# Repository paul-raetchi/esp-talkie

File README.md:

# esp-talkie
ESP8266-based WiFi 802.11b/g/n Walkie Talkie

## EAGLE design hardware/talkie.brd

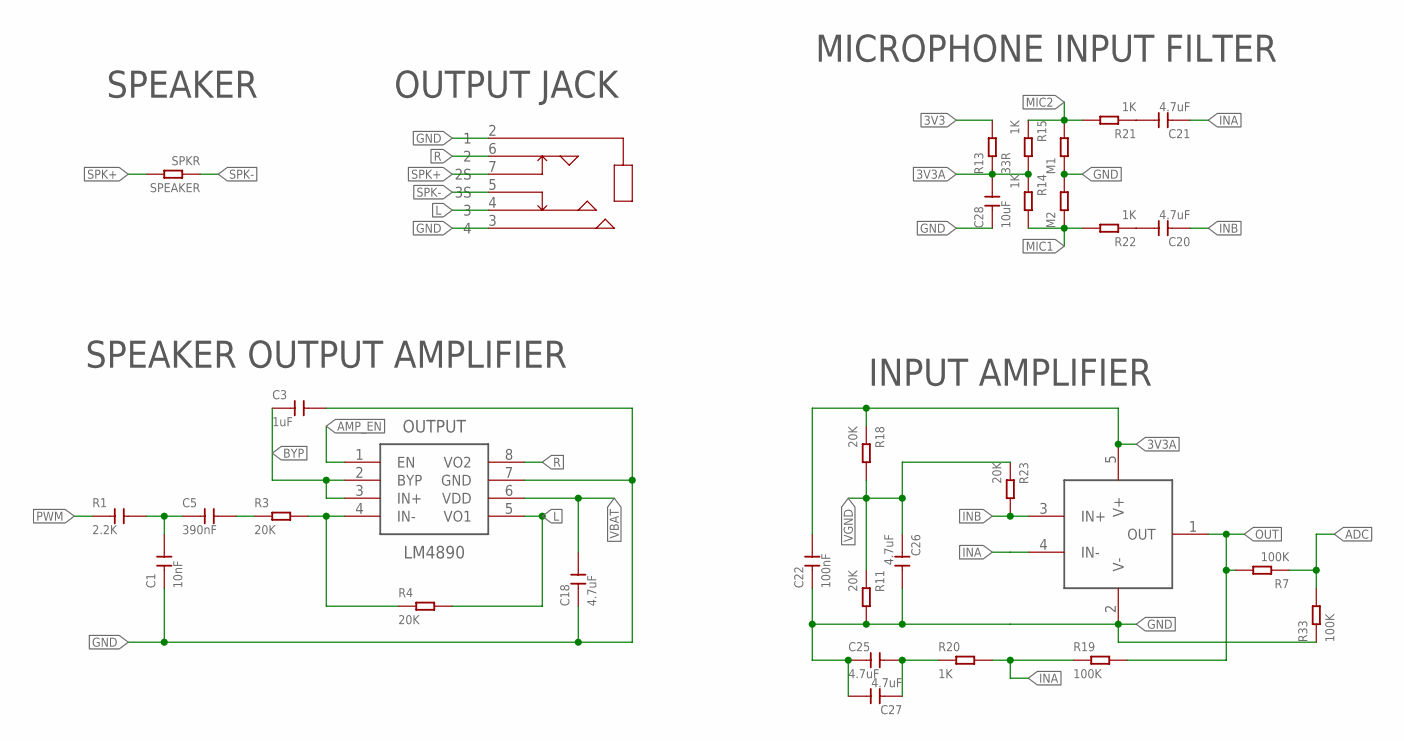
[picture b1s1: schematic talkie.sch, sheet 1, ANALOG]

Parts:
C1: 10nF; C0402
C3: 1uF; C0402
C5: 390nF; C0402
C18, C20, C21, C25, C26, C27: 4.7uF; C0402
C22: 100nF; C0402
C28: 10uF; C0603
JACK: PJ-342; PJ-342-6P
M1, M2: RES-1206; R1206
OUTPUT: LM4890; 8-MSOP
PREAMP: MCP6001UT-I; SOT-23-5
R1: 2.2K; C0402
R3, R4, R11, R18, R23: 20K; R0402
R7, R19, R33: 100K; R0402
R13: 33R; R0402
R14, R15, R20, R21, R22: 1K; R0402
SPEAKER: SPKR; R1206

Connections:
3V3: R13.2; also elsewhere on the board
3V3A: C22.2, C28.2, PREAMP.5 (V+), R13.1, R14.1, R15.2, R18.1
ADC: R7.1, R33.2; also elsewhere on the board
AMP_EN: OUTPUT.1 (EN); also elsewhere on the board
BYP: C3.1, OUTPUT.2 (BYP), OUTPUT.3 (IN+)
DAC: OUTPUT.4 (IN-), R3.2, R4.1
GND: C1.1, C3.2, C18.1, C22.1, C25.1, C26.2, C27.2, C28.1, JACK.2 (1), JACK.3 (4), M1.1, M2.2, OUTPUT.7 (GND), PREAMP.2 (V-), R11.2, R33.1; also elsewhere on the board
HIGHPASS: C5.2, R3.1
INA: C21.1, PREAMP.4 (IN-), R19.1, R20.2
INAG: C25.2, C27.1, R20.1
INB: C20.1, PREAMP.3 (IN+), R23.2
L: JACK.4 (3), OUTPUT.5 (VO1), R4.2
LOWPASS: C1.2, C5.1, R1.2
MIC1: M2.1, R14.2, R22.2
MIC2: M1.2, R15.1, R21.2
unnamed: C21.2, R21.1
unnamed: C20.2, R22.1
OUT: PREAMP.1 (OUT), R7.2, R19.2
PWM: R1.1; also elsewhere on the board
R: JACK.6 (2), OUTPUT.8 (VO2)
SPK+: JACK.7 (2S), SPEAKER.2
SPK-: JACK.5 (3S), SPEAKER.1
VBAT: C18.2, OUTPUT.6 (VDD); also elsewhere on the board
VGND: C26.1, R11.1, R18.2, R23.1

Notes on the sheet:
SPEAKER OUTPUT AMPLIFIER
MICROPHONE INPUT FILTER
INPUT AMPLIFIER
OUTPUT JACK
SPEAKER

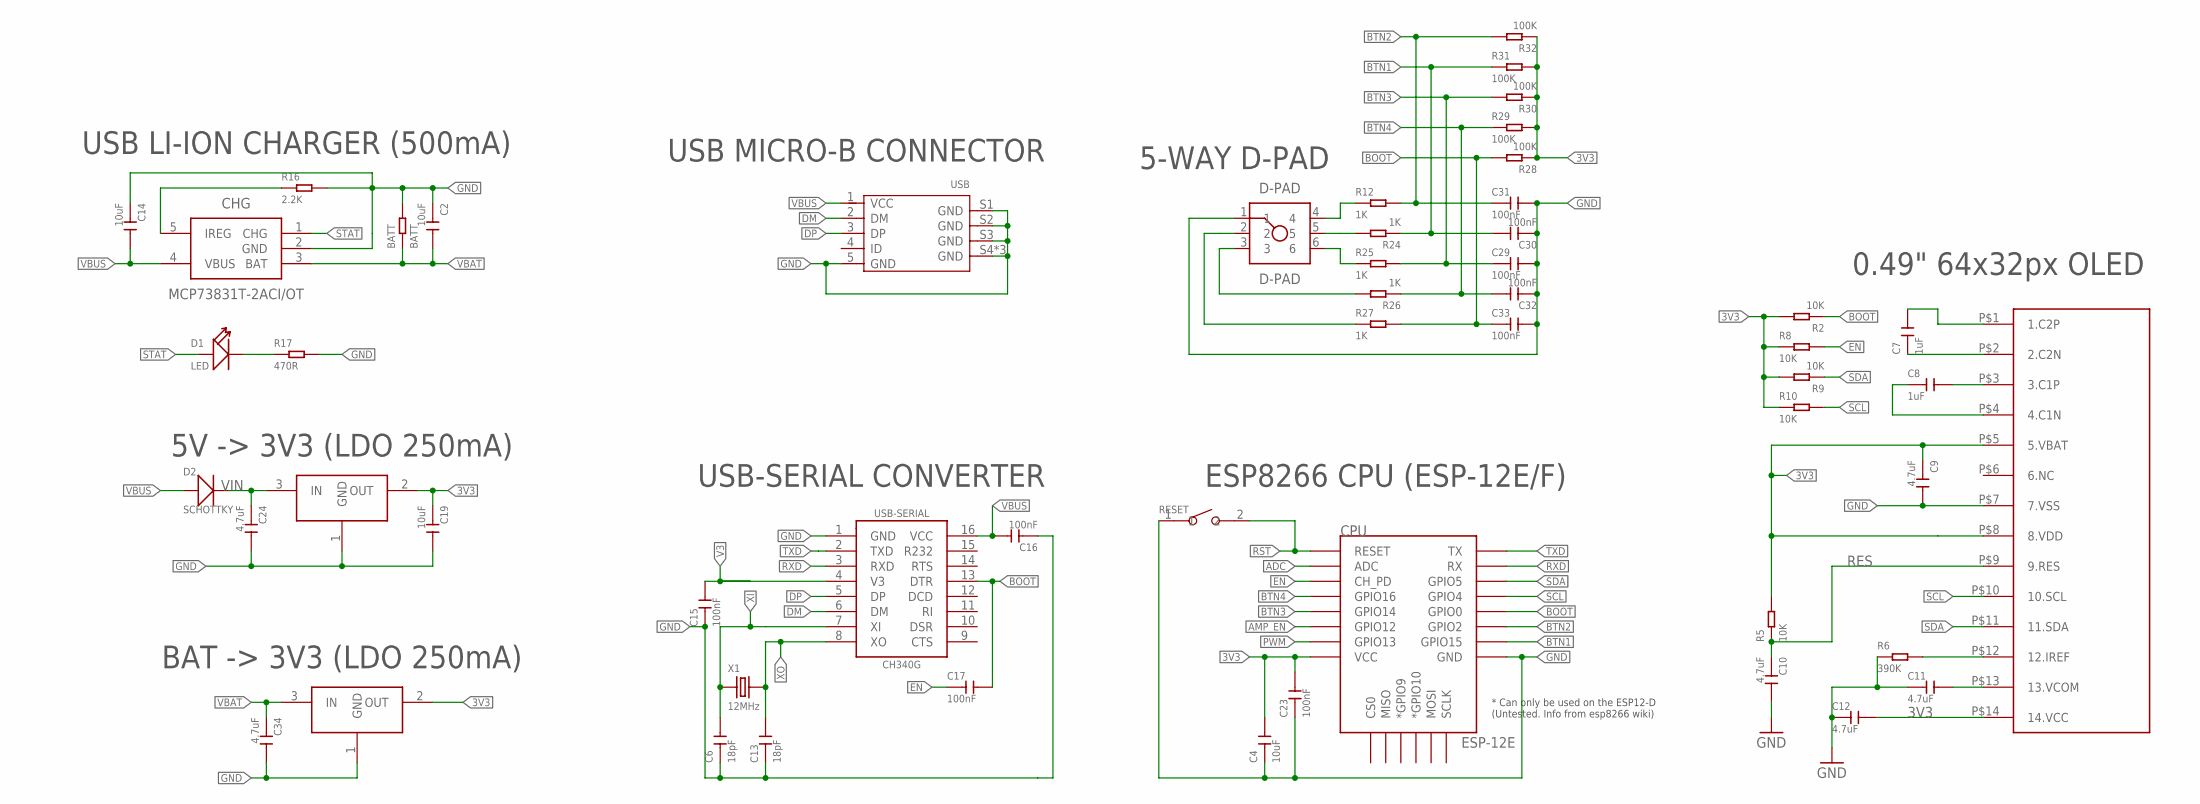
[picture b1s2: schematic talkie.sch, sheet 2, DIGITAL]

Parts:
BATT: BATT; R1206
C2, C4, C14, C19: 10uF; C0603
C6, C13: 18pF; C0402
C7, C8: 1uF; C0402
C9, C10, C11, C12, C24, C34: 4.7uF; C0402
C15, C16, C17, C23, C29, C30, C31, C32, C33: 100nF; C0402
CHG: MCP73831T-2ACI/OT; SOT-23-5
CPU: ESP-12E; ESP12E-SMD
D1: LED; LED-0402
D2: SCHOTTKY; SOD-123
D-PAD: D-PAD; DPAD-10X10
LDO1: MCP1700T; SOT-23-3
LDO2: MCP1700T-3302E; SOT-23-3
OLED: ER-OLED0.49
R2, R5, R8, R9, R10: 10K; R0402
R6: 390K; R0402
R12, R24, R25, R26, R27: 1K; R0402
R16: 2.2K; R0402
R17: 470R; R0402
R28, R29, R30, R31, R32: 100K; R0402
RESET: SMD-BUTTON(2P-3.0X2.5X1.2+0.4MM)-B3U-1000P-2P-SMD; SW2-2.6-3.0X2.5X1.2+0.4MM
USB: MICRO-USB-SMD-B-WITHOUT-POST-W/P(ST-USB-001G); MICRO-USB5+4P-SMD-0.65-B
USB-SERIAL: CH340G; 16-SSOP
X1: 12MHz; X4-SMD-3.2X2.5X0.7MM

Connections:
3V3: C4.2, C9.1, C12.2, C19.1, C23.2, CPU.VCC, LDO1.2 (OUT), LDO2.2 (OUT), OLED.P$5 (5.VBAT), OLED.P$8 (8.VDD), OLED.P$14 (14.VCC), R2.2, R5.2, R8.1, R9.2, R10.1, R28.1, R29.2, R30.1, R31.2, R32.1; also elsewhere on the board
ADC: CPU.ADC; also elsewhere on the board
AMP_EN: CPU.GPIO12; also elsewhere on the board
B1: D-PAD.4, R12.1
B2: D-PAD.5, R24.2
B3: D-PAD.6, R25.1
B4: D-PAD.3, R26.2
B5: D-PAD.2, R27.1
BOOT: C17.2, C33.1, CPU.GPIO0, R2.1, R27.2, R28.2, USB-SERIAL.13 (DTR)
BTN1: C30.2, CPU.GPIO15, R24.1, R31.1
BTN2: C31.1, CPU.GPIO2, R12.2, R32.2
BTN3: C29.1, CPU.GPIO14, R25.2, R30.2
BTN4: C32.2, CPU.GPIO16, R26.1, R29.1
C1N: C8.1, OLED.P$4 (4.C1N)
C1P: C8.2, OLED.P$3 (3.C1P)
C2N: C7.1, OLED.P$2 (2.C2N)
C2P: C7.2, OLED.P$1 (1.C2P)
DM: USB.2 (DM), USB-SERIAL.6 (DM)
DP: USB.3 (DP), USB-SERIAL.5 (DP)
EN: C17.1, CPU.CH_PD, R8.2
GND: BATT.2, C2.1, C4.1, C6.1, C9.2, C10.2, C11.1, C12.1, C13.1, C14.1, C15.1, C16.1, C19.2, C23.1, C24.2, C29.2, C30.1, C31.2, C32.1, C33.2, C34.2, CHG.2 (GND), CPU.GND, D-PAD.1, LDO1.1 (GND), LDO2.1 (GND), OLED.P$7 (7.VSS), R6.1, R16.2, R17.2, RESET.1, USB.5 (GND), USB.S1 (GND), USB.S2 (GND), USB.S3 (GND), USB.S4 (GND), USB.S5 (GND), USB.S6 (GND), USB-SERIAL.1 (GND); also elsewhere on the board
IREF: OLED.P$12 (12.IREF), R6.2
LED: D1.-, R17.1
PROG: CHG.5 (IREG), R16.1
PWM: CPU.GPIO13; also elsewhere on the board
RES: C10.1, OLED.P$9 (9.RES), R5.1
RST: CPU.RESET, RESET.2
RXD: CPU.RXD0 (RX), USB-SERIAL.3 (RXD)
SCL: CPU.GPIO4, OLED.P$10 (10.SCL), R10.2
SDA: CPU.GPIO5, OLED.P$11 (11.SDA), R9.1
STAT: CHG.1 (CHG), D1.+
TXD: CPU.TXD0 (TX), USB-SERIAL.2 (TXD)
V3: C15.2, USB-SERIAL.4 (V3)
VBAT: BATT.1, C2.2, C34.1, CHG.3 (BAT), LDO1.3 (IN); also elsewhere on the board
VBUS: C14.2, C16.2, CHG.4 (VBUS), D2.+, USB.1 (VCC), USB-SERIAL.16 (VCC)
VCOM: C11.2, OLED.P$13 (13.VCOM)
VIN: C24.1, D2.-, LDO2.3 (IN)
XI: C6.2, USB-SERIAL.7 (XI), X1.1
XO: C13.2, USB-SERIAL.8 (XO), X1.3 (2)

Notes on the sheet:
5V -> 3V3 (LDO 250mA)
USB MICRO-B CONNECTOR
USB LI-ION CHARGER (500mA)
USB-SERIAL CONVERTER
0.49" 64x32px OLED
ESP8266 CPU (ESP-12E/F)
5-WAY D-PAD
BAT -> 3V3 (LDO 250mA)

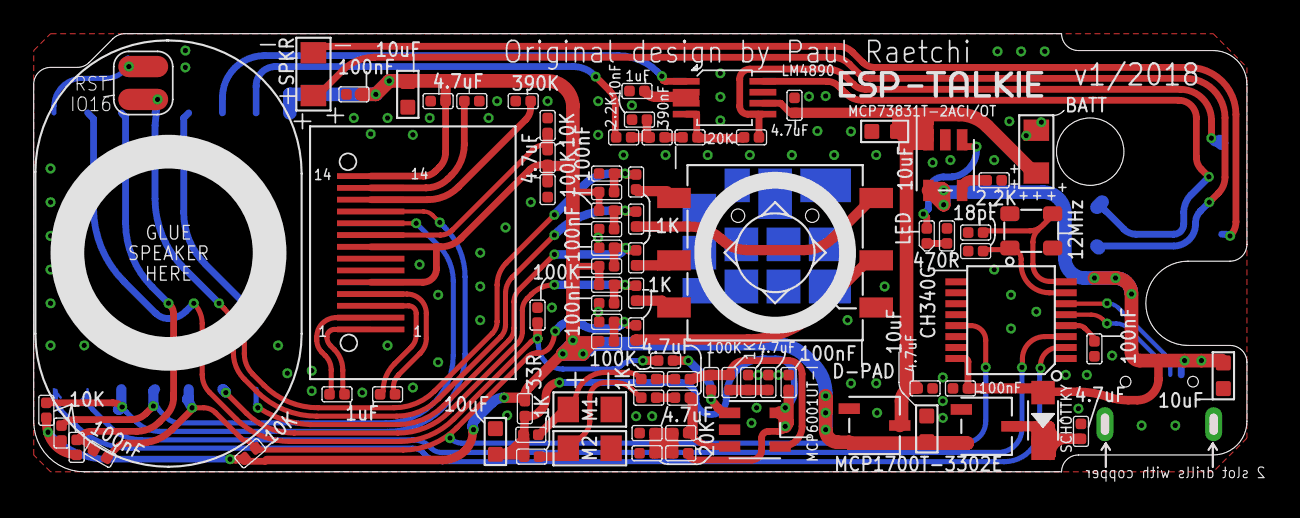
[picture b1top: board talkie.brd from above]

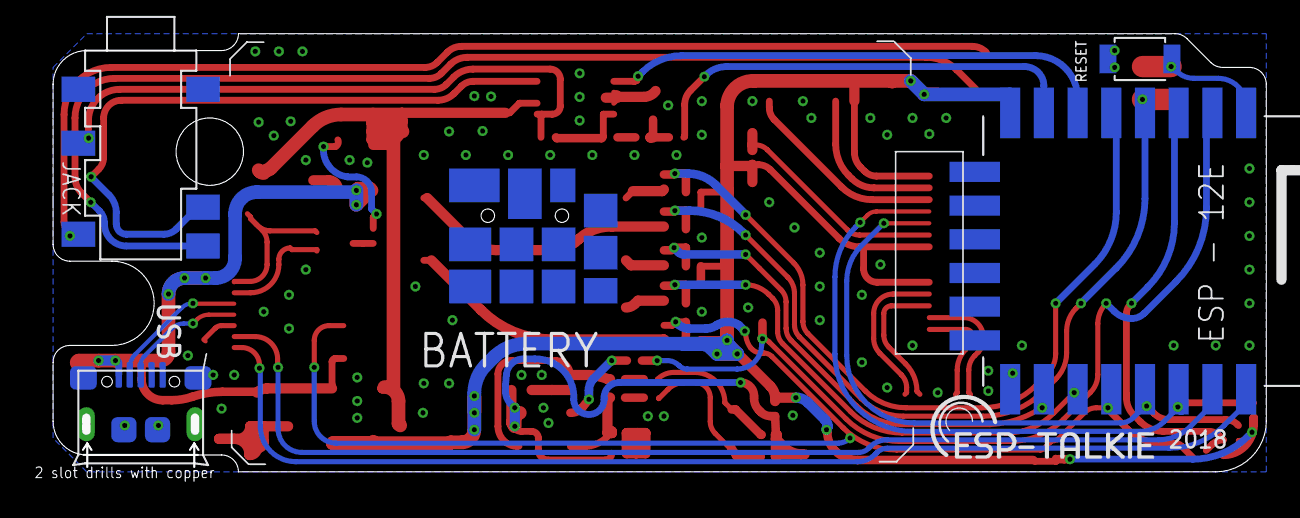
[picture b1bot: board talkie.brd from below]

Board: 2 copper layers, 72.6 x 26.2 mm, 86 parts (4 on the bottom side), 57 nets.

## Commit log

2018-07-21 Added Eagle schematic + layout + library
2018-07-22 Added screenshots. Moved design files to folders
2018-07-27 Latest files (also sent to pcbway and jlcpcb)

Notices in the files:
parts and their libraries:
SparkFun-Aesthetics: Licensing: CC v3.0 Share-Alike You are welcome to use this library for commercial purposes.
